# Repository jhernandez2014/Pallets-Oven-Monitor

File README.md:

# PALLETS OVEN MONITOR

## Instrucciones para Instalar Mysql

1. Actualizar la lista de paquete: `sudo apt-get update && sudo apt-get upgrade`
2. Instalamos el MySQL actual: `sudo apt-get install mariadb-server`
3. Al finalizar ejecutamos el comando para inciar la configurarcion: `sudo mysql_secure_installation`
4. Agregamos el nuevo password: `dtr+123` 
5. Comprobamos la intalación con el comando: `mysql --version`
6. Para acceder al CLI de MySQL usamos el siguiente comando. `sudo mysql -u root -p -h localhost`

## Instrucciones para Instalar Node js
Para poder instalar una version ARM de Node:

1. `curl -sL https://deb.nodesource.com/setup_14.x | sudo -E bash -` 
2. `sudo apt install -y nodejs`
Basicamente es todo. Solo debes esperar a que se decargue e instale.

Para verificar que este instalado correctamente, use el comando `node -v`. De esta forma, podrá ver la versión de node

## Instrucciones para Instalar el Proyecto

1. Instalamos git: `sudo apt-get install git`
1. Para clonar el repositorio, nos dirigimos a: `cd /var`
1. Creamos una carpeta que contendrá el Proyecto: `sudo mkdir www`
1. Para evitar el uso de `sudo` cuando se desea colocar los archivos en el web raíz , se puede cambiar el propietario a su usuario Pi , y el grupo al `www-data` , que es utilizado por Nginx : `sudo chown -R pi:www-data www`
1. Clonamos el repositorio: `git clone http://git.doter.mx/doter/Pallets-Oven-Monitor.git`
1. Ingresamos al proyecto: `cd /Pallets-Oven-Monitor`
1. Instalamos los packetes: `npm install`
1. Editamos la configuración de la base de datos: `config/database.js`
1. Creamos el esquema de la base de datos: `node scripts/create_database.js`
1. Corremos el server.js para verificar: `node server.js`
1. Ingresa a tu navegador con la direccion: `http://localhost:8080`
1. Ahora creamos un `.sh` para iniciar el server.js: `sudo nano start.sh`
1. Pegamos lo siquiente: 
```sleep 5
   cd /var/www/Pallets-Oven-Monitor
   sleep 1
   sudo node server.js```
1. Guardamos y Cerramos.
1. Creamos un nuevo crontab para que cada que reinicie, levante el node: `crontab -e`
1. Al final del archivo, escribimos la siguiente linea: `@reboot sudo sh /home/pi/start.sh &`
1. Guardamos y cerramos.

### Ahora instalamos Nginx.

1. Actualizamos la lista de paquetes: `sudo apt-get update`
1. Instalamos Nginx con el comando: `sudo apt-get install nginx`
1. Cuando la instalacion este completa, iniciamos el server : `sudo service nginx start`

### Configuramos Nginx como servidor:

1. Nos posicionamos en la siguiente dirección:  `cd /etc/nginx/sites-available/`
1. Editamos el documento default:  `sudo nano default`
```
server {
   listen 80;
   root /var/www/Pallets-Oven-Monitor/;                  # identifies the location of the application you are configuring
   server_name _;                 # identifies the hostname used by this application's traffic
   location / {
      proxy_pass http://127.0.0.1:8080/;   # configures the back-end destination for this traffic
      proxy_http_version 1.1;
      proxy_set_header Upgrade $http_upgrade;
      proxy_set_header Connection 'upgrade';
      proxy_set_header Host $host;
      proxy_cache_bypass $http_upgrade;
   }
}
```
1. Reiniciamos el servicio para activar los cambios: `sudo service nginx reload`

### Configuramos el Hostname de la Raspi:

1. Instalamos Avahi: `sudo apt-get install avahi-daemon`
1. Ya instalado, configuramos el Host: `sudo nano /etc/hosts`
1. Deja todas las entradas a excepción de la última `127.0.1.1` etiquetada con el nombre de host `"Raspberry Pi"`. Esta es la única línea que desea editar . Reemplazar `"Raspberry Pi"` con cualquier nombre de host que desee . Hemos sustituido en nuestro dispositivo con `"Pallets"` . Presione CTRL + X para cerrar el editor ; de acuerdo con sobreescribir el archivo existente y guardarlo
1. Devuelta ala teminal, editamos el Hostname: `sudo nano /etc/hostname`
1. Remplace el hostaname default `" Raspberry Pi "` por defecto con el mismo nombre de host del paso anterior
1. Por último , hay que confirmar los cambios en el sistema y reinicie el sistema para que los cambios surtan efecto. En la terminal , introduzca el siguiente comando para confirmar los cambios : `sudo /etc/init.d/hostname.sh`
1. Ahora reinicie: `sudo reboot`

## Instrucciones para Instalar Script Poweroff & Reboot

1. El script se encuentra en: `Pallets-Oven-Monitor/python/power.py`
1. Copiamos el script a la carpeta "pi": 
```
    cp /var/www/Pallets-Oven-Monitor/python/start.sh /home/pi/
    cp /var/www/Pallets-Oven-Monitor/python/power.py /home/pi/
    cp /var/www/Pallets-Oven-Monitor/python/hornoDB2.py /home/pi/
```
1. Creamos un nuevo crontabe: `crontab -e` 
1. Al final del archivo ponemos las siguiente linea: 
```
    @reboot sudo python /home/pi/start.sh &
    @reboot sudo python /home/pi/power.py &
    @reboot sudo python /home/pi/hornoDB2.py &
```

### Nota!! Los pines de la GPIO configurados son: `17 para Apagado` y `27 para Reiniciar`

## Instrucciones para instalar Chromium Browser

1. wget http://ftp.us.debian.org/debian/pool/main/libg/libgcrypt11/libgcrypt11_1.5.0-5+deb7u3_armhf.deb
1. wget http://launchpadlibrarian.net/218525709/chromium-browser_45.0.2454.85-0ubuntu0.14.04.1.1097_armhf.deb
1. wget http://launchpadlibrarian.net/218525711/chromium-codecs-ffmpeg-extra_45.0.2454.85-0ubuntu0.14.04.1.1097_armhf.deb
1. sudo dpkg -i libgcrypt11_1.5.0-5+deb7u3_armhf.deb
1. sudo dpkg -i chromium-codecs-ffmpeg-extra_45.0.2454.85-0ubuntu0.14.04.1.1097_armhf.deb
1. sudo dpkg -i chromium-browser_45.0.2454.85-0ubuntu0.14.04.1.1097_armhf.deb

### Configurar Para iniciar desde Boot

1. Haga clic en el menú de inicio , seleccione INTERNET , a continuación, haga clic derecho en Chromium Browser , y hace clic en el icono de enviar al escritorio.
1. seguimos los siguientes comandos: 
1. `sudo cp /home/pi/Desktop/chromium-browser.desktop /home/pi/.config/autostart/chromium-browser.desktop`
1. `cd /home/pi/.config/autostart/`
1. `sudo leafpad chromium-browser.desktop`
1. Busca la linea que diga : `Exec=chromium-browser %u` y remplacelo por : `python /home/pi/.config/MPKPyTimer/pytimer4.py`
1. Ahora Creamos un script para correr Chromium como kiosk:
1. `cd /home/pi/.config`
1. `mkdir MKPyTimer`
1. `cd MKPyTimer`
1. `touch pytimer4.py `
1. Modificamos el archivo: sudo leafpad pytimer4.py
1. El script inicia el Browser Full Screen e Ingresa a localhost 

```
import os
from time import *

sleep(10)
os.system('chromium-browser --kiosk --disable-infobars --disable-session-crashed-bubble "http://localhost/login"')```
```
1. Guardar y salir.

## Modificar detalles de Boot

1. Para quitar el logo del Boot. Agregamos` logo.nologo` al archivo `/boot/cmdline.txt`.
1. Configuramos el overscren_left,right,top y bottom a 0 y rotamos la pantalla `lcd_rotate=2` en el archivo `/boot/config.txt`
1. Para quitar el icono en el boton de Menu, damos click derecho sobre de este y seleccionamos `Menu Settings`, ahi podremos cambiar la imagen.
1. Para cambiar el fondo de pantalla: click derecho sobre el backgraound y seleccionar `Desktop Preference`, en la opcion de `Wallpaper`, podremos cambiar la imagen de fondo.

#Referencias
* [Instalar MySql](https://pimylifeup.com/raspberry-pi-mysql/)
* [Instalar Node](https://thisdavej.com/beginners-guide-to-installing-node-js-on-a-raspberry-pi/)
* [Modulo de Sensor](https://www.mouser.mx/ProductDetail/Maxim-Integrated/MAX31865PMB1?qs=%2fha2pyFadugzPBIFKo2sF67U9oxj3Brsz1xuhHOjWnkrBiEkgg6ehA%3d%3d)

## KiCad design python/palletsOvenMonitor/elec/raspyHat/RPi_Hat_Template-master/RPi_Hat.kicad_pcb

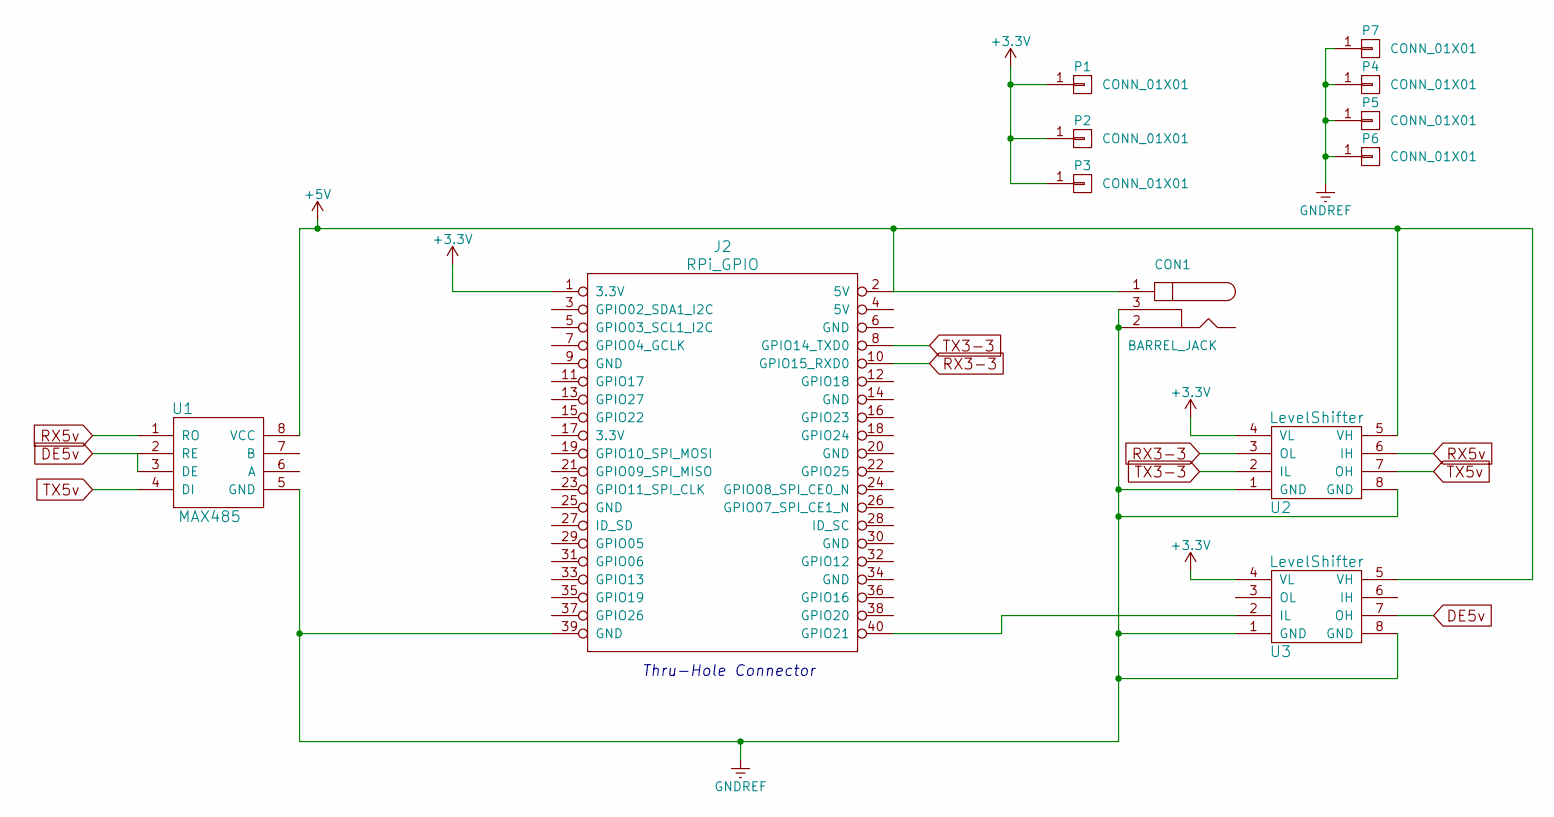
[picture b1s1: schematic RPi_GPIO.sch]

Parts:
CON1: BARREL_JACK
J2: RPi_GPIO; Pin_Header_Straight_2x20
P1, P2, P3, P4, P5, P6, P7: CONN_01X01; SolderWirePad_single_1-2mmDrill
U1: MAX485; MAX485-PdxLbs
U2, U3: LevelShifter; LEVELSHIFTER

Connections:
+3V3: J2.1 (3.3V), P1.1, P2.1, P3.1, U2.4 (VL), U3.4 (VL)
+5V: CON1.1, J2.2 (5V), U1.8 (VCC), U2.5 (VH), U3.5 (VH)
DE5v: U1.2 (RE), U1.3 (DE), U3.7 (OH)
GNDREF: CON1.2, CON1.3, J2.39 (GND), P4.1, P5.1, P6.1, P7.1, U1.5 (GND), U2.1 (GND), U2.8 (GND), U3.1 (GND), U3.8 (GND)
unnamed: J2.40 (GPIO21), U3.2 (IL)
RX3-3: J2.10 (GPIO15_RXD0), U2.3 (OL)
RX5v: U1.1 (RO), U2.6 (IH)
TX3-3: J2.8 (GPIO14_TXD0), U2.2 (IL)
TX5v: U1.4 (DI), U2.7 (OH)

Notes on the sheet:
Thru-Hole Connector

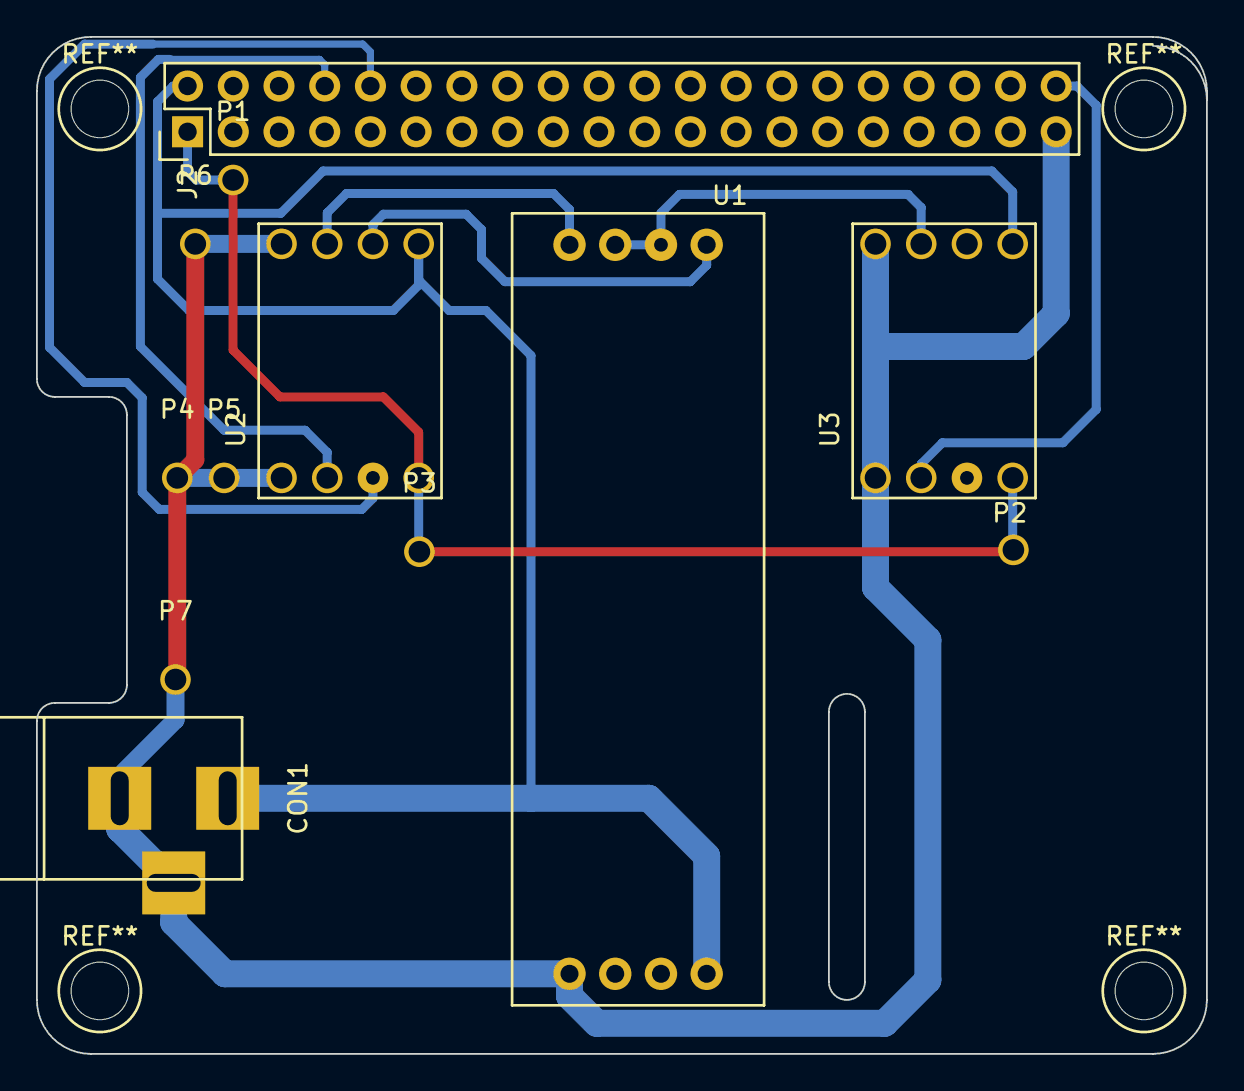
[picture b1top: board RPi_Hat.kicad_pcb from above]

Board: 2 copper layers, 65.0 x 56.5 mm, 12 parts (0 on the bottom side), 9 nets.

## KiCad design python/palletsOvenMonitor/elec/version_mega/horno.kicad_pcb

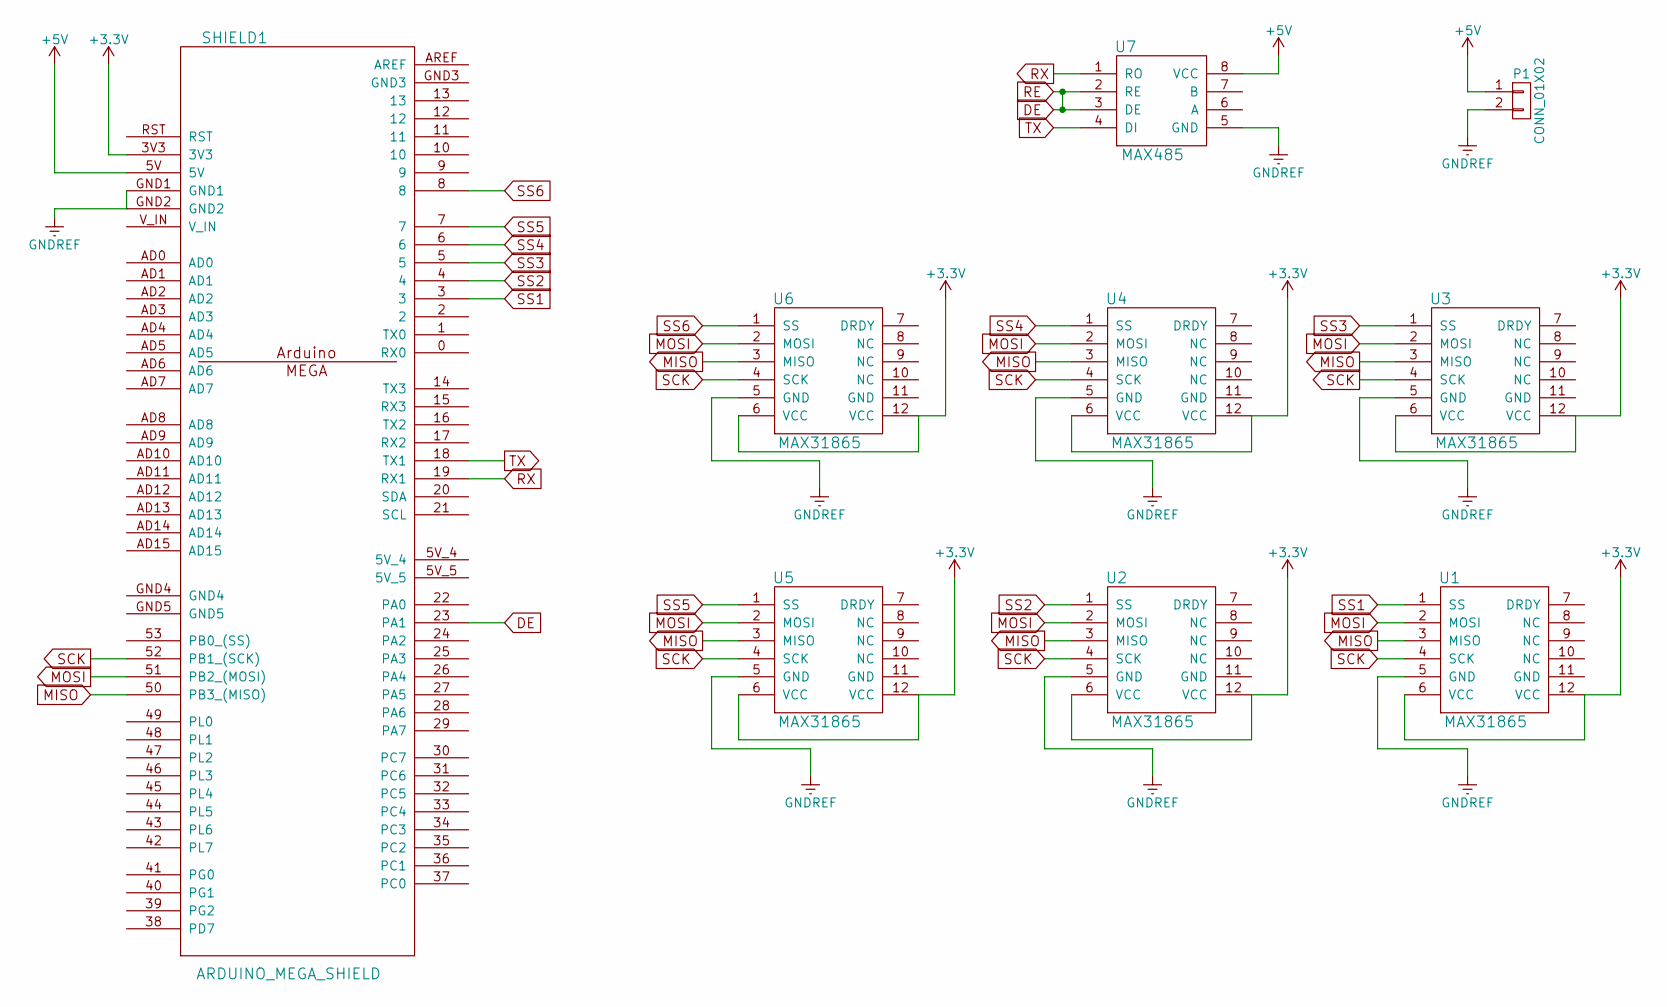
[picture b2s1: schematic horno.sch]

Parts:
P1: CONN_01X02; bornier2
SHIELD1: ARDUINO_MEGA_SHIELD; ARDUINO MEGA SHIELD
U1, U2, U3, U4, U5, U6: MAX31865; MAX31865-Module-PdxLbs
U7: MAX485; MAX485-PdxLbs

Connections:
+3V3: SHIELD1.3V3, U1.6 (VCC), U1.12 (VCC), U2.6 (VCC), U2.12 (VCC), U3.6 (VCC), U3.12 (VCC), U4.6 (VCC), U4.12 (VCC), U5.6 (VCC), U5.12 (VCC), U6.6 (VCC), U6.12 (VCC)
+5V: P1.1, SHIELD1.5V, U7.8 (VCC)
DE: SHIELD1.23 (PA1), U7.2 (RE), U7.3 (DE)
GNDREF: P1.2, SHIELD1.GND1, SHIELD1.GND2, U1.5 (GND), U2.5 (GND), U3.5 (GND), U4.5 (GND), U5.5 (GND), U6.5 (GND), U7.5 (GND)
MISO: SHIELD1.50 (PB3_(MISO)), U1.3 (MISO), U2.3 (MISO), U3.3 (MISO), U4.3 (MISO), U5.3 (MISO), U6.3 (MISO)
MOSI: SHIELD1.51 (PB2_(MOSI)), U1.2 (MOSI), U2.2 (MOSI), U3.2 (MOSI), U4.2 (MOSI), U5.2 (MOSI), U6.2 (MOSI)
RX: SHIELD1.19 (RX1), U7.1 (RO)
SCK: SHIELD1.52 (PB1_(SCK)), U1.4 (SCK), U2.4 (SCK), U3.4 (SCK), U4.4 (SCK), U5.4 (SCK), U6.4 (SCK)
SS1: SHIELD1.3, U1.1 (SS)
SS2: SHIELD1.4, U2.1 (SS)
SS3: SHIELD1.5, U3.1 (SS)
SS4: SHIELD1.6, U4.1 (SS)
SS5: SHIELD1.7, U5.1 (SS)
SS6: SHIELD1.8, U6.1 (SS)
TX: SHIELD1.18 (TX1), U7.4 (DI)

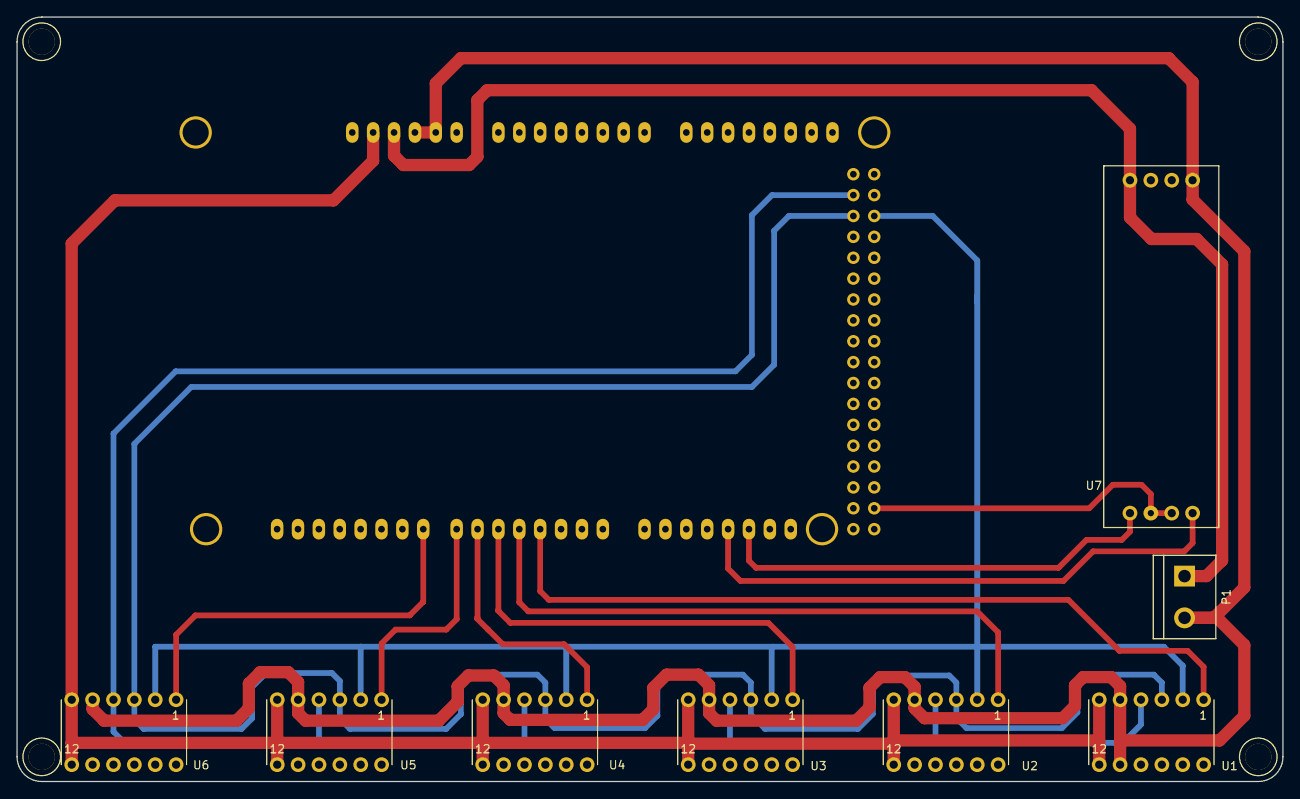
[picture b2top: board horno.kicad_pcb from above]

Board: 2 copper layers, 154.0 x 93.0 mm, 9 parts (1 on the bottom side), 15 nets.

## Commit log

2022-08-16 first proyect
